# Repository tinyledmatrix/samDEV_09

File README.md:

# samDEV_09
small test/development board for Atmels's SAMD09 ARM Cortex M0+ Microcontroller

see my [poject](https://hackaday.io/project/12099) on Hackaday.io for more information. 

I build this board to getting started with the SAMD microcontroller family after I made the mistake to try the much bigger SAMD21 first. The SAMD09 used here is he smallest from this family and therefore has the shortest (still 709 p.) datasheet. I think this board will be, as my other microcontroller breakout boards, very useful for an early prototyping phase on breadboard. So far I quite like the SAMD09. If you compare it to the the ATmegas there are a lot more possibilities. Maybe this is the Arduino Nano killer for me.
Features

    - 3.3V 0.8A LDO (1117-3.3)
    - powered from USB, Vin pin (3.6-13.8V) or regulated 3.3V
    - on board USB to serial bride IC (CH340)
    - reset switch
    - SWD programming header
    - optional 32kHz crystal (if not needed pins can be used as additional IOs)
    - on board user LED (connected to PA02)
    - on board power LED (connected to 3.3 rail)

###Partlist:

    Part   Value        Package     Comment          
    A08                 0603        User LED connected to PA08
    C1     100n         C0603       
    C2     15p          C0603       optional 
    C3     15p          C0603       optional 
    C4     10n          C0603       
    C5     100n         C0603       
    C7     100n         C0603       
    D1     MBR0520LT    SOD123      power selection diode
    D2     MBR0520LT    SOD123      power selection diode
    IC1    CH340G       SOIC16      USB-UART bridge
    IC2    1117-3.3     SOT223      LDO
    JP1                 1X08_OCTA   pin header
    JP2                 1X08_OCTA   pin header
    JP5                 2X05_1,27B  programming pin header 
    K1     mini USB     generic     Mini USB connector
    PWR                 0603 	Power LED
    Q1     3215         3215        optional external 32kHz crystal 
    Q2     CSTCRCSTCE   CSTCESMALL  12 MHz resonator for CH340G
    R1     solder / 0   R0201       PA08 - pin header
    R2     solder / 0   R0201       PA09 - pin header
    R3     120  / 220   R0603       resistor for power LED
    R4     120  / 220   R0603       resistor for user LED
    R5     ~10k         R0603       pullup for reset
    S2                  SMDSWITCH   Chinese SMD switch
    U$1    SAMD09SOIC14 SO14        ARM Cortex M0+ microcontroller

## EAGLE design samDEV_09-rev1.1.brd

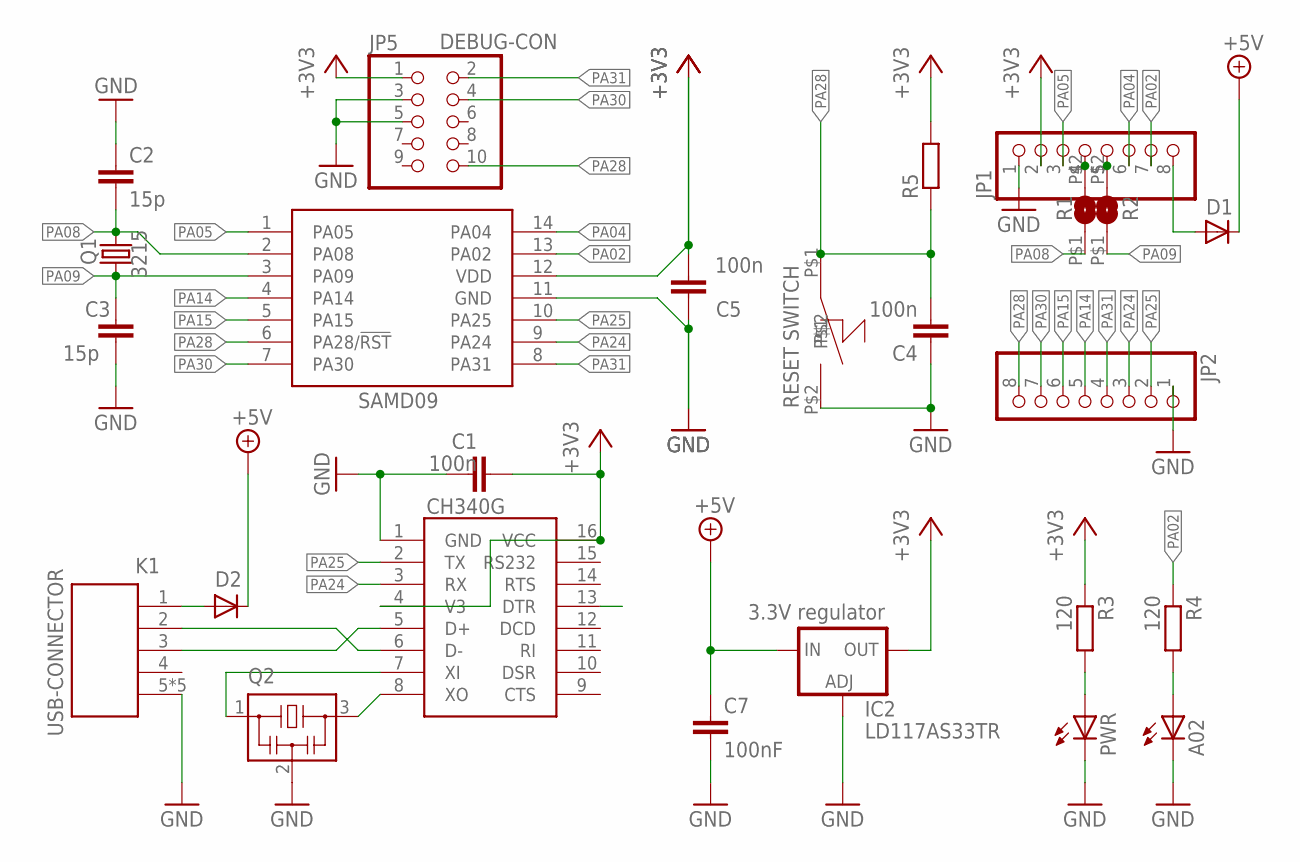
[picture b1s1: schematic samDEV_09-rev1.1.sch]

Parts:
A02: LEDCHIPLED_0603; CHIPLED_0603
C1, C4, C5: 100n; C0603
C2, C3: 15p; C0603
C7: 100nF; C0603
D1, D2: MBR0520LT; SOD123
IC1: CH340G; SOIC16
IC2: LD117AS33TR; SOT223
JP1, JP2: PINHD-1X8OCTA; 1X08_OCTA
JP5: PINHD-2X51272; 2X05_1,27B
K1: 629105136821
PWR: LEDCHIPLED_0603; CHIPLED_0603
Q1: 3215
Q2: CSTCRCSTCE_SMALL_FOOT; CSTCESMALL
R1, R2: SJAL; SMD_AL1
R3, R4: 120; R0603
R5: R-EU_R0603; R0603
S2: SMD_SWITCH; SMDSWITCH
U$1: SAMD09SOIC14; SO14

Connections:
+3V3: C1.2, C5.2, IC1.4 (V3), IC1.16 (VCC), IC2.2 (OUT), IC2.4 (OUT), JP1.2, JP5.1, R3.1, R5.2, U$1.12 (VDD)
+5V: C7.1, D1.C, D2.C, IC2.3 (IN)
GND: A02.C, C1.1, C2.1, C3.2, C4.1, C5.1, C7.2, IC1.1 (GND), IC2.1 (ADJ), JP1.1, JP2.1, JP5.3, JP5.5, K1.5, K1.Z1 (5), K1.Z2 (5), K1.Z3 (5), K1.Z4 (5), PWR.C, Q2.2, S2.P$2, U$1.11 (GND)
unnamed: D1.A, JP1.8
unnamed: D2.A, K1.1
unnamed: PWR.A, R3.2
unnamed: JP1.4, R1.P$2 (2)
unnamed: JP1.5, R2.P$2 (2)
unnamed: A02.A, R4.2
unnamed: IC1.6 (D-), K1.2
unnamed: IC1.5 (D+), K1.3
unnamed: IC1.8 (XO), Q2.3
unnamed: IC1.7 (XI), Q2.1
PA02: JP1.7, R4.1, U$1.13 (PA02)
PA04: JP1.6, U$1.14 (PA04)
PA05: JP1.3, U$1.1 (PA05)
PA08: C2.2, Q1.2, R1.P$1 (1), U$1.2 (PA08)
PA09: C3.1, Q1.1, R2.P$1 (1), U$1.3 (PA09)
PA14: JP2.5, U$1.4 (PA14)
PA15: IC1.13 (DTR), JP2.6, U$1.5 (PA15)
PA24: IC1.3 (RX), JP2.3, U$1.9 (PA24)
PA25: IC1.2 (TX), JP2.2, U$1.10 (PA25)
PA28: C4.2, JP2.8, JP5.10, R5.1, S2.P$1, U$1.6 (PA28/!RST)
PA30: JP2.7, JP5.4, U$1.7 (PA30)
PA31: JP2.4, JP5.2, U$1.8 (PA31)

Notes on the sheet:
SAMD09
DEBUG-CON
RESET SWITCH
USB-CONNECTOR
3.3V regulator

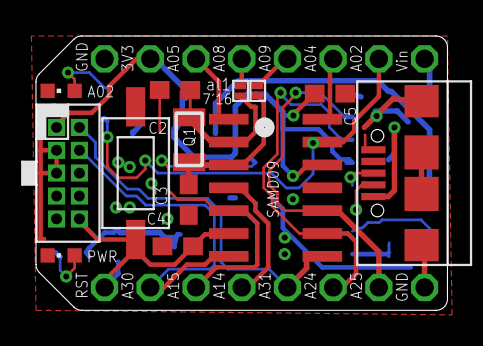
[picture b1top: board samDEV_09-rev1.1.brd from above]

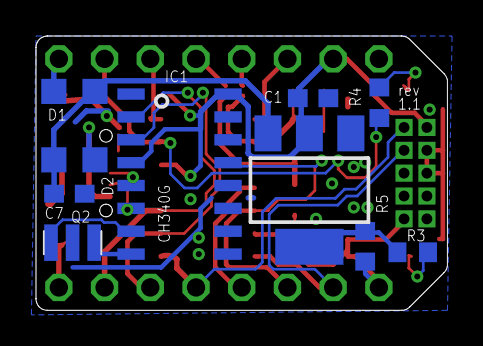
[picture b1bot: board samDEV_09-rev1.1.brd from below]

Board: 2 copper layers, 22.9 x 15.2 mm, 25 parts (10 on the bottom side), 25 nets.

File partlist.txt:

samDEV_09 Part list

Part   Value        Package     Comment
                    
A08                 0603        User LED connected to PA08
C1     100n         C0603       
C2     15p          C0603       optional (use only if external crystal used)
C3     15p          C0603       optional (use only if external crystal used)
C4     10n          C0603       
C5     100n         C0603       
C7     100n         C0603       
D1     MBR0520LT    SOD123      power selection diode
D2     MBR0520LT    SOD123      power selection diode
IC1    CH340G       SOIC16      USB-UART bridge
IC2    1117-3.3     SOT223      LDO
JP1                 1X08_OCTA   pin header
JP2                 1X08_OCTA   pin header
JP5                 2X05_1,27B  programming pin header 
K1     mini USB     generic     Mini USB connector
PWR                 0603 	   Power LED
Q1     3215         3215        optional external 32kHz crystal 
Q2     CSTCRCSTCE   CSTCESMALL  12 MHz resonator for CH340G
R1     solder / 0   R0201       solder jumper to connect PA08 to pin header
R2     solder / 0   R0201       solder jumper to connect PA09 to pin header
R3     120  / 220   R0603       resistor for power LED
R4     120  / 220   R0603       resistor for user LED
R5     ~10k         R0603       pullup for reset
S2                  SMDSWITCH   Chinese SMD switch
U$1    SAMD09SOIC14 SO14        Atmel SAMD09 ARM Cortex M0+ microcontroller

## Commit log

2016-06-05 added schematic
2016-06-18 blik examole
2016-06-19 added UART example
2016-06-19 replaced taps with spaces
2016-06-20 added partlist
2016-07-06 added bootloader files
2016-07-06 updated bootloader readme
2016-07-06 bootloader update
2016-07-16 added SPI libary
2016-07-17 updated SPI readme
    mow there is some example code in the SPI readme how to use rhis library
2016-07-17 readme SPI
2016-07-17 added spi-flash stuff
    some early code for spi flash
2016-07-25 SPI update
    now also working with clocks, which are not the default 1MHz
2016-10-01 Added gerbersof rev1.1
2016-10-01 eagle files of rev 1.1
2016-10-01 readme update
2017-02-02 Hex file for blink.c

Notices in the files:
parts and their libraries:
USBSteckverbinderWR-COM: Copyright: Würth Elektronik
